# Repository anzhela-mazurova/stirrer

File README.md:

# stirrer
Magnetic stirrer for 1 US gallon bottle. The following information is provided:

1. Mechanical drawings of all 3D-printed parts in FreeCAD format.
2. Electronics Schematic and Board design in Eagle CAD format.
3. Source code of Board firmware.

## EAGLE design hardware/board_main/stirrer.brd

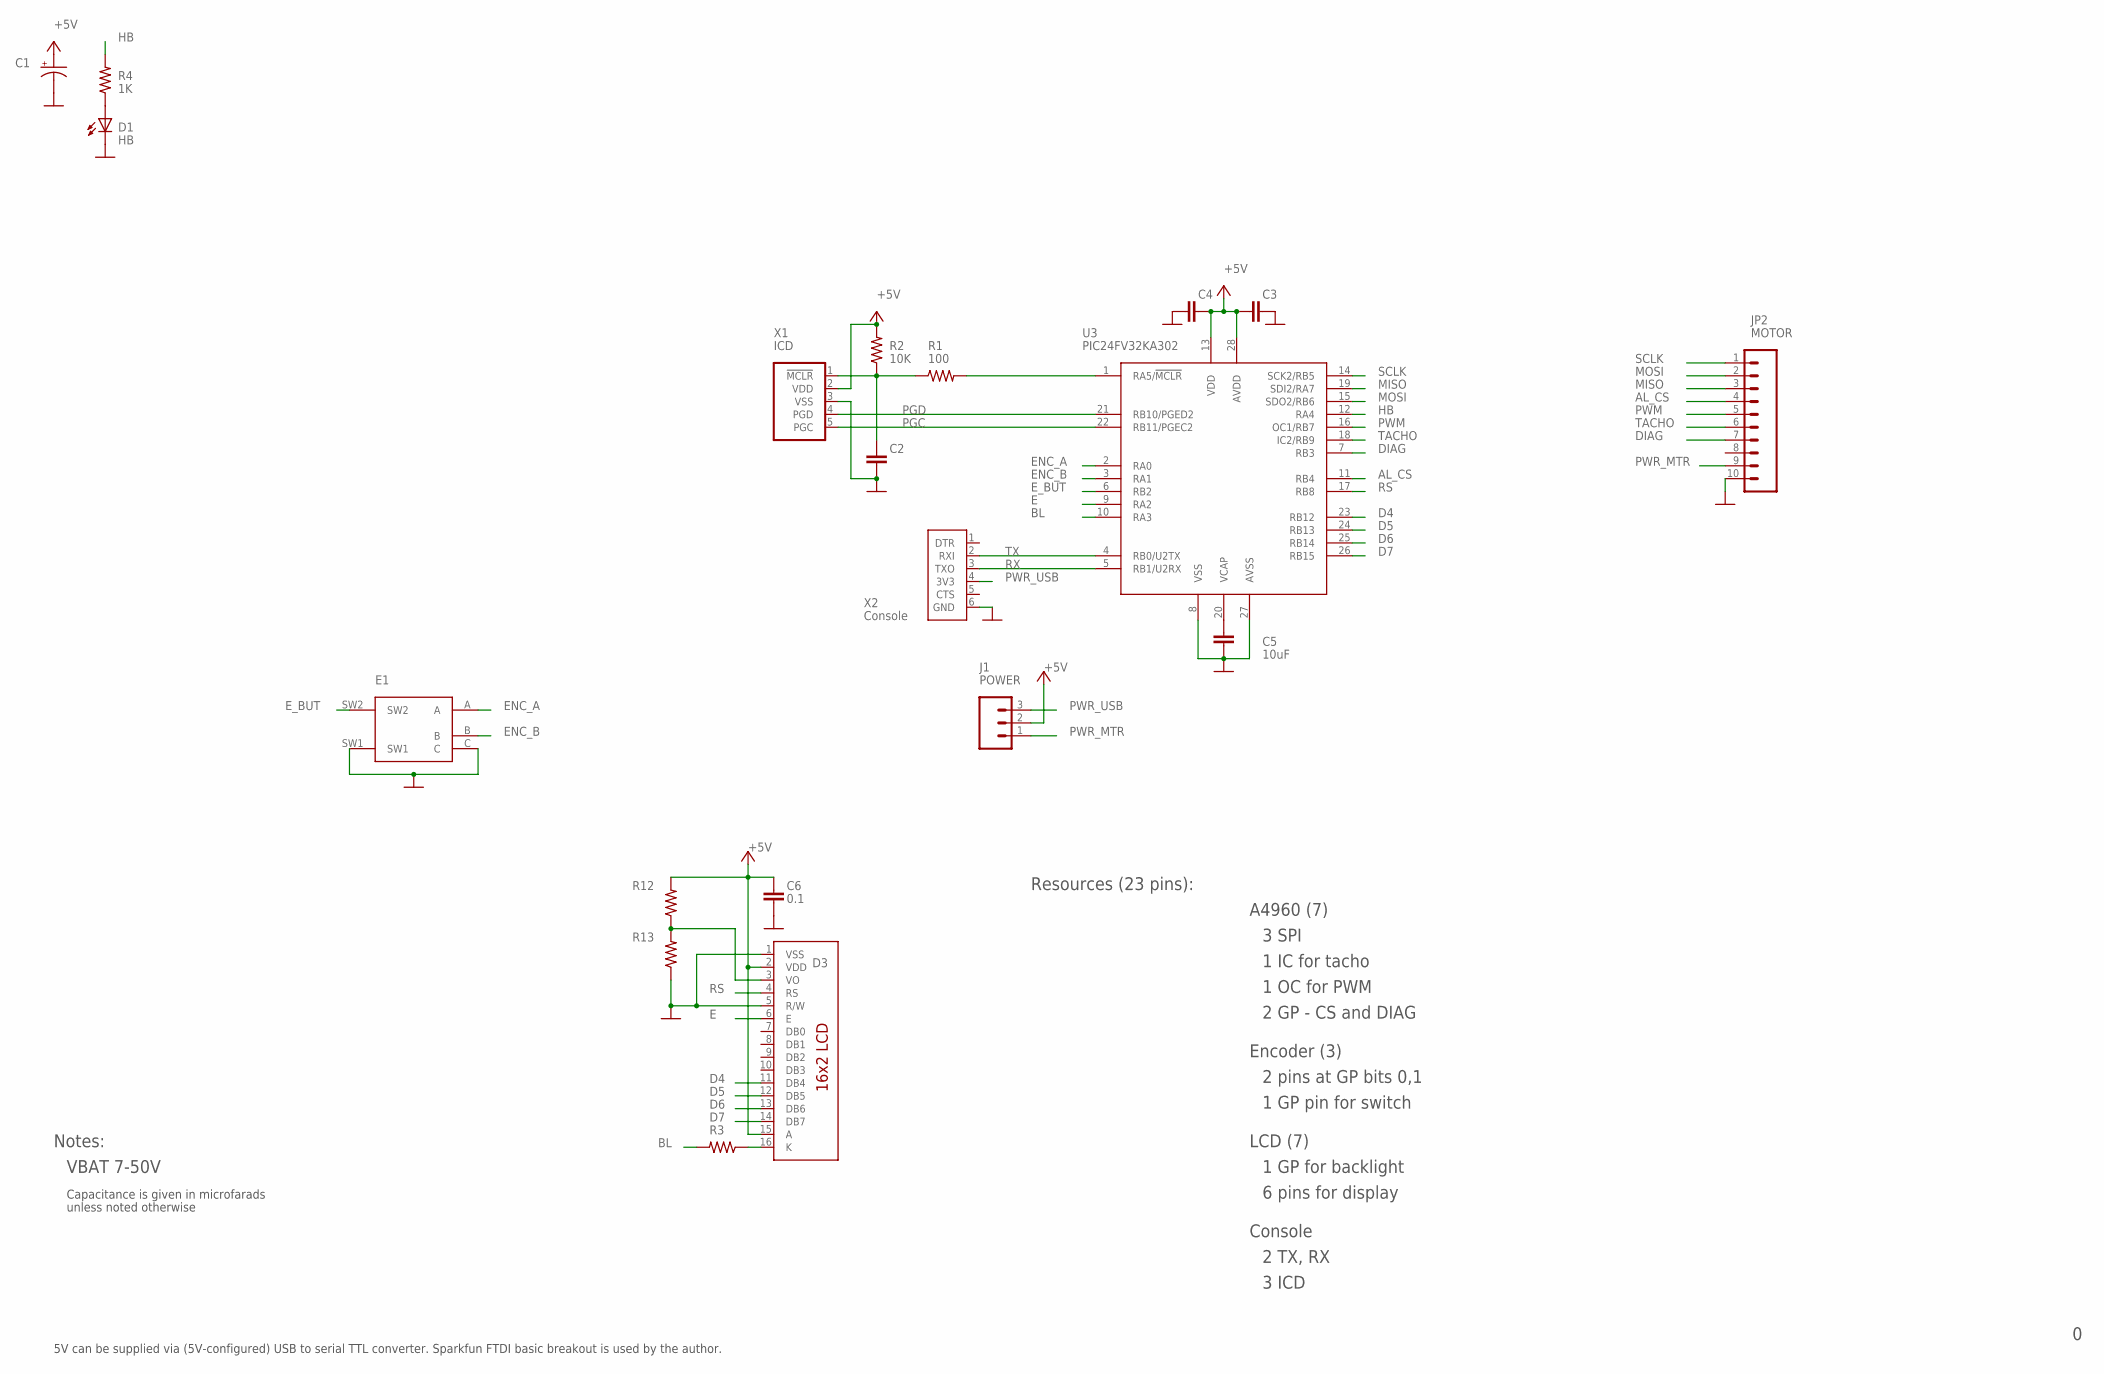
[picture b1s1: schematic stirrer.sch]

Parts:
C1: CAP_POL-RAD4; CAP_RAD_4MM
C2, C3, C4: 0.1uF; CAP-PTH-SMALL
C5: 10uF; CAP-PTH-SMALL
C6: 0.1; CAP-PTH-SMALL
D1: HB; LED5MM
D3: LCD-16X2-STD; LCD-16X2
E1: ROTARY_ENCODER_SWITCH-PEC12_HOR; ENC_12X14MM_SW_HOR
J1: POWER; 1X03
JP2: MOTOR; 1X10
R1: 100; AXIAL-0.4
R2: 10K; AXIAL-0.4
R3, R12, R13: RESISTOR-PTH04; AXIAL-0.4
R4: 1K; AXIAL-0.4
U3: PIC24FV32KA302; DIL28-3
X1: ICD; 1X05
X2: Console; 1X06

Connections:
+5V: C1.P (+), C3.1, C4.2, C6.2, D3.2 (VDD), D3.15 (A), J1.2, R2.P$2 (2), R12.P$2 (2), U3.13 (VDD), U3.28 (AVDD), X1.2 (VDD)
AL_CS: JP2.4, U3.11 (RB4)
BL: R3.P$2 (2), U3.10 (RA3)
D4: D3.11 (DB4), U3.23 (RB12)
D5: D3.12 (DB5), U3.24 (RB13)
D6: D3.13 (DB6), U3.25 (RB14)
D7: D3.14 (DB7), U3.26 (RB15)
DIAG: JP2.7, U3.7 (RB3)
E: D3.6 (E), U3.9 (RA2)
ENC_A: E1.A, U3.2 (RA0)
ENC_B: E1.B, U3.3 (RA1)
E_BUT: E1.SW2, U3.6 (RB2)
GND: C1.N (-), C2.1, C3.2, C4.1, C5.2, C6.1, D1.K (C), D3.1 (VSS), D3.5 (R/W), E1.C, E1.SW1, JP2.10, R13.P$1 (1), U3.8 (VSS), U3.27 (AVSS), X1.3 (VSS), X2.6 (GND)
HB: R4.P$2 (2), U3.12 (RA4)
MISO: JP2.3, U3.19 (SDI2/RA7)
MOSI: JP2.2, U3.15 (SDO2/RB6)
unnamed: C5.1, U3.20 (VCAP)
unnamed: R1.P$2 (2), U3.1 (RA5/!MCLR)
unnamed: D3.16 (K), R3.P$1 (1)
unnamed: D1.A, R4.P$1 (1)
unnamed: D3.3 (VO), R12.P$1 (1), R13.P$2 (2)
unnamed: C2.2, R1.P$1 (1), R2.P$1 (1), X1.1 (!MCLR)
PGC: U3.22 (RB11/PGEC2), X1.5 (PGC)
PGD: U3.21 (RB10/PGED2), X1.4 (PGD)
PWM: JP2.5, U3.16 (OC1/RB7)
PWR_MTR: J1.1, JP2.9
PWR_USB: J1.3, X2.4 (3V3)
RS: D3.4 (RS), U3.17 (RB8)
RX: U3.5 (RB1/U2RX), X2.3 (TXO)
SCLK: JP2.1, U3.14 (SCK2/RB5)
TACHO: JP2.6, U3.18 (IC2/RB9)
TX: U3.4 (RB0/U2TX), X2.2 (RXI)

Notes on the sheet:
Notes:
VBAT 7-50V
Resources (23 pins):
3 SPI
6 pins for display
2 GP - CS and DIAG
A4960 (7)
1 IC for tacho
1 OC for PWM
Encoder (3)
2 pins at GP bits 0,1
1 GP pin for switch
LCD (7)
1 GP for backlight
Console
2 TX, RX
3 ICD
Capacitance is given in microfarads
unless noted otherwise
5V can be supplied via (5V-configured) USB to serial TTL converter. Sparkfun FTDI basic breakout is used by the author.

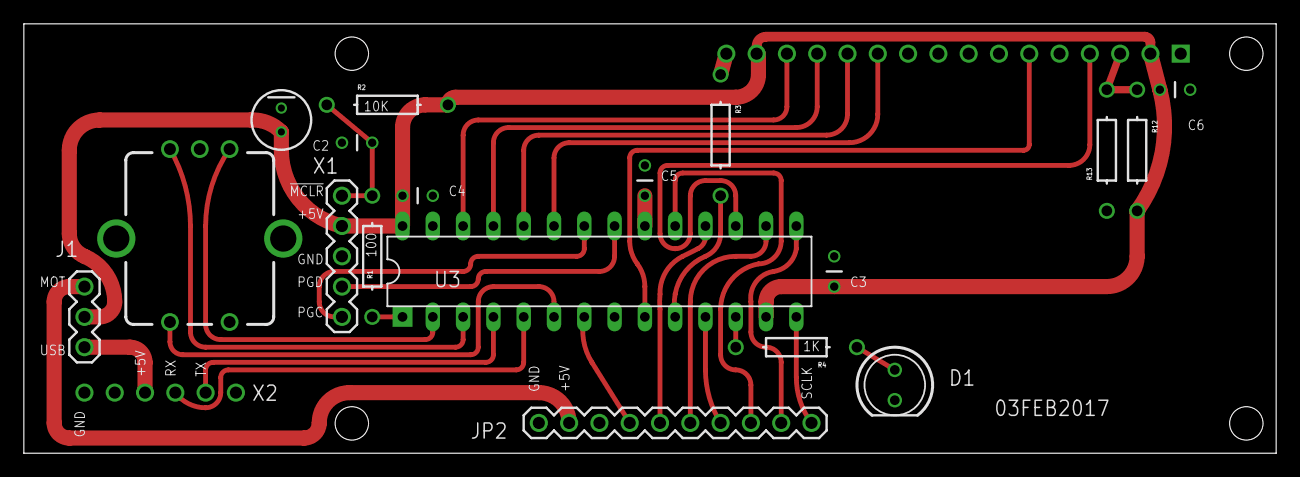
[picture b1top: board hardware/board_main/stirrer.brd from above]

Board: 2 copper layers, 105.0 x 36.0 mm, 20 parts (1 on the bottom side), 32 nets.

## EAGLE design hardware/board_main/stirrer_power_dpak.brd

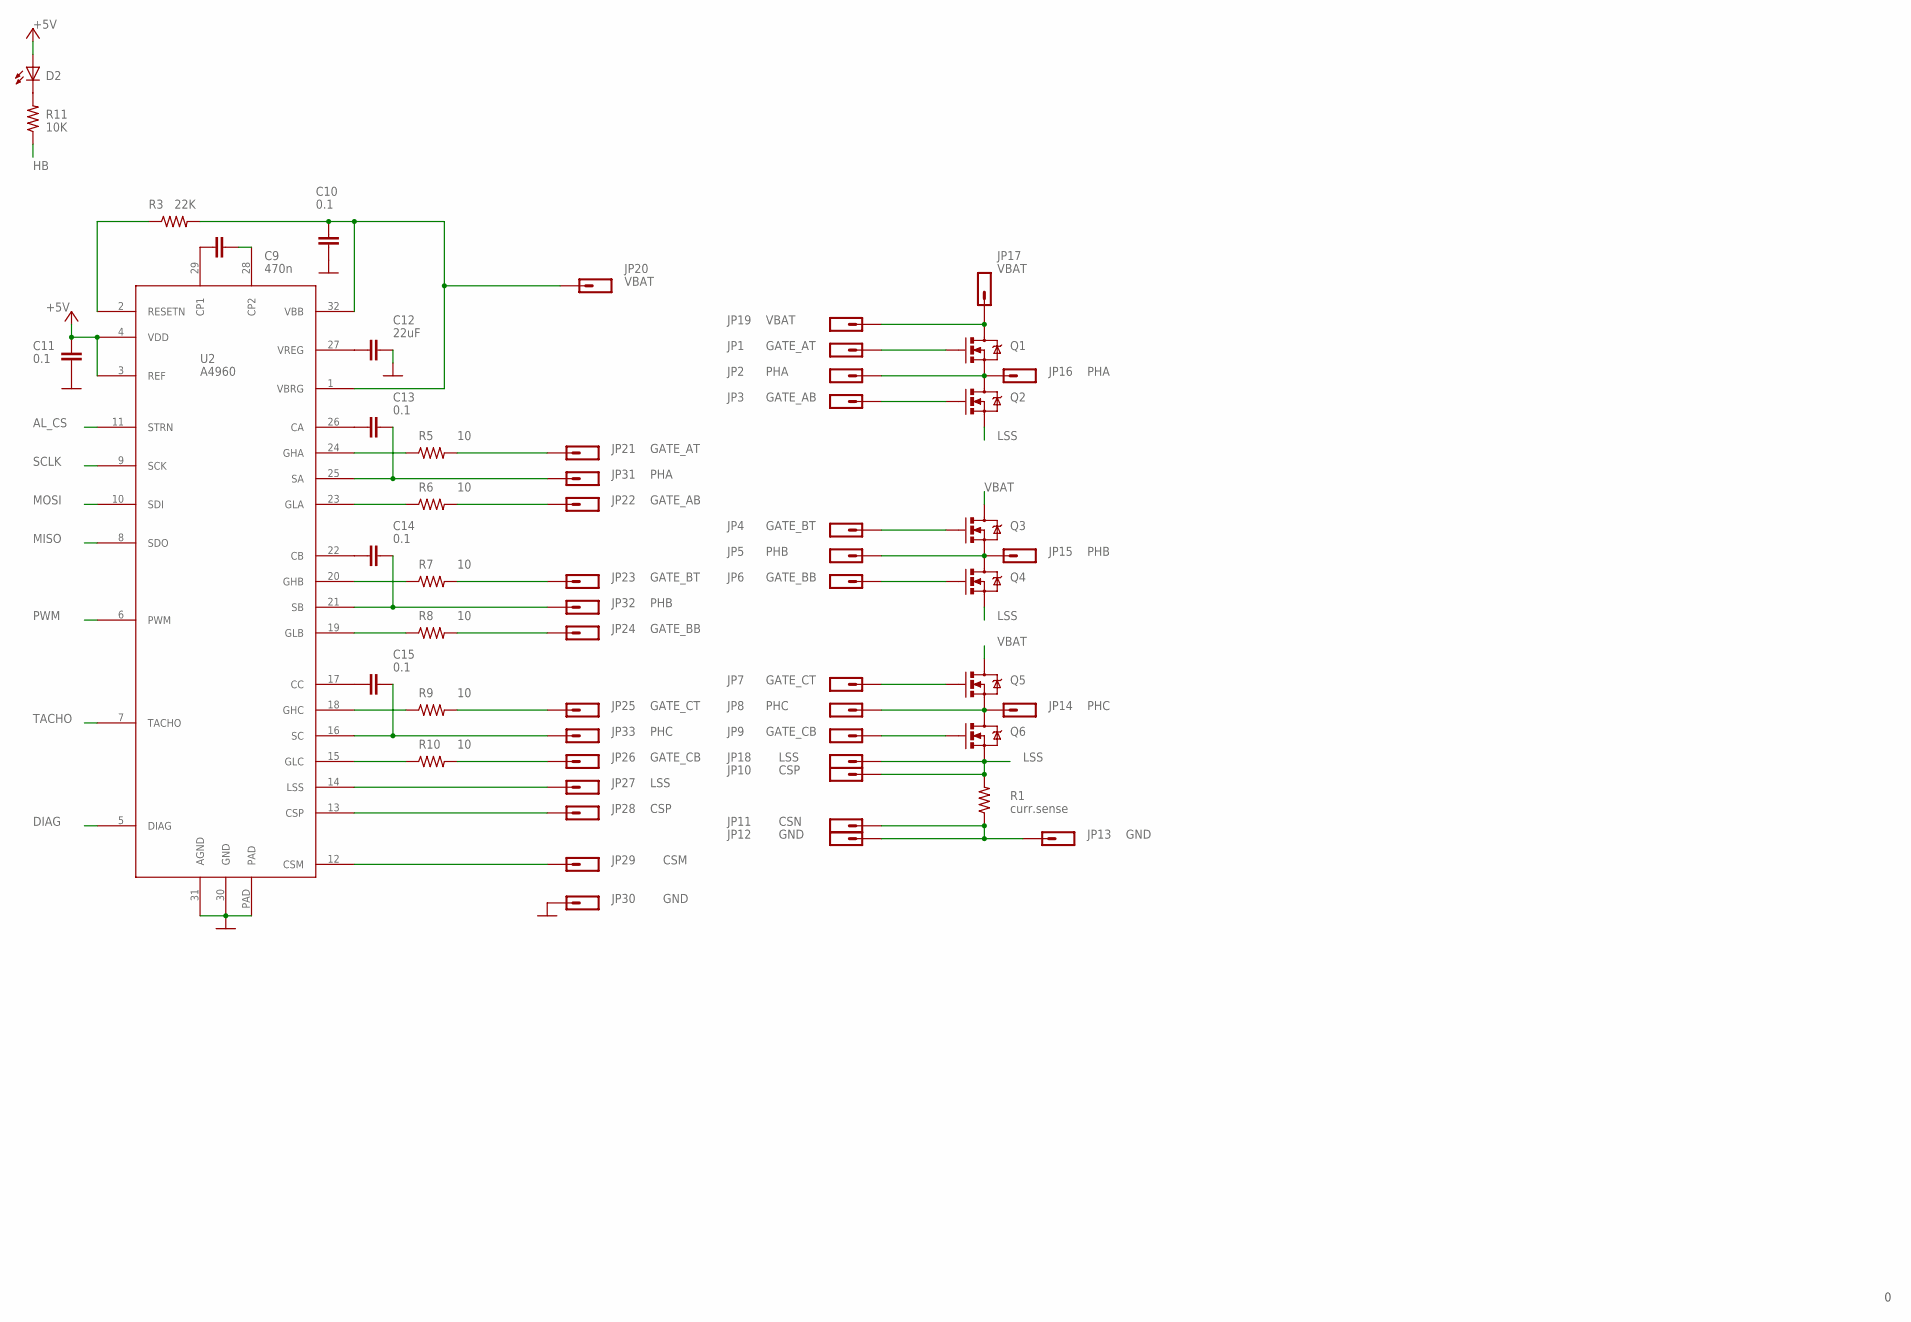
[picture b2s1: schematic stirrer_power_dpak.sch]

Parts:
C9: 470n; 0603
C10, C11, C13, C14, C15: 0.1; 0603
C12: 22uF; 1206
D2: LED5MM
JP1, JP21: GATE_AT; 1X01_TT
JP2, JP16, JP31: PHA; 1X01_TT
JP3, JP22: GATE_AB; 1X01_TT
JP4, JP23: GATE_BT; 1X01_TT
JP5, JP15, JP32: PHB; 1X01_TT
JP6, JP24: GATE_BB; 1X01_TT
JP7, JP25: GATE_CT; 1X01_TT
JP8, JP14, JP33: PHC; 1X01_TT
JP9, JP26: GATE_CB; 1X01_TT
JP10, JP28: CSP; 1X01_TT
JP11: CSN; 1X01_TT
JP12, JP13, JP30: GND; 1X01_TT
JP17, JP19, JP20: VBAT; 1X01_TT
JP18, JP27: LSS; 1X01_TT
JP29: CSM; 1X01_TT
Q1, Q2, Q3, Q4, Q5, Q6: MOSFET-NCHANNEL-DPAK; DPAK
R1: curr.sense; 2512
R3: 22K; 0603
R5, R6, R7, R8, R9, R10: 10; 0603
R11: 10K; 0603
U2: A4960; LQPF-32

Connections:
+5V: C11.2, D2.A, U2.3 (REF), U2.4 (VDD)
AL_CS: U2.11 (STRN)
CSM: JP29.1, U2.12 (CSM)
CSP: JP28.1, U2.13 (CSP)
DIAG: U2.5 (DIAG)
GATE_AB: JP22.1, R6.2
GATE_AT: JP21.1, R5.2
GATE_BB: JP24.1, R8.2
GATE_BT: JP23.1, R7.2
GATE_CB: JP26.1, R10.2
GATE_CT: JP25.1, R9.2
GND: C10.1, C11.1, C12.2, JP11.1, JP12.1, JP13.1, JP30.1, R1.P$1 (1), U2.30 (GND), U2.31 (AGND), U2.PAD
HB: R11.1
LSS: JP10.1, JP18.1, Q2.3 (S), Q4.3 (S), Q6.3 (S), R1.P$2 (2)
LSS1: JP27.1, U2.14 (LSS)
MISO: U2.8 (SDO)
MOSI: U2.10 (SDI)
unnamed: JP2.1, JP16.1, Q1.3 (S), Q2.4 (D)
unnamed: JP5.1, JP15.1, Q3.3 (S), Q4.4 (D)
unnamed: JP8.1, JP14.1, Q5.3 (S), Q6.4 (D)
unnamed: JP1.1, Q1.1 (G)
unnamed: JP3.1, Q2.1 (G)
unnamed: C9.1, U2.29 (CP1)
unnamed: C9.2, U2.28 (CP2)
unnamed: R3.1, U2.2 (RESETN)
unnamed: D2.K (C), R11.2
unnamed: JP4.1, Q3.1 (G)
unnamed: JP6.1, Q4.1 (G)
unnamed: JP7.1, Q5.1 (G)
unnamed: JP9.1, Q6.1 (G)
unnamed: C12.1, U2.27 (VREG)
unnamed: C13.2, U2.26 (CA)
unnamed: C14.2, U2.22 (CB)
unnamed: C15.2, U2.17 (CC)
unnamed: C13.1, JP31.1, U2.25 (SA)
unnamed: C14.1, JP32.1, U2.21 (SB)
unnamed: C15.1, JP33.1, U2.16 (SC)
unnamed: R5.1, U2.24 (GHA)
unnamed: R7.1, U2.20 (GHB)
unnamed: R9.1, U2.18 (GHC)
unnamed: R6.1, U2.23 (GLA)
unnamed: R8.1, U2.19 (GLB)
unnamed: R10.1, U2.15 (GLC)
PWM: U2.6 (PWM)
SCLK: U2.9 (SCK)
TACHO: U2.7 (TACHO)
VBAT: JP17.1, JP19.1, Q1.4 (D), Q3.4 (D), Q5.4 (D)
VBAT1: C10.2, JP20.1, R3.2, U2.1 (VBRG), U2.32 (VBB)

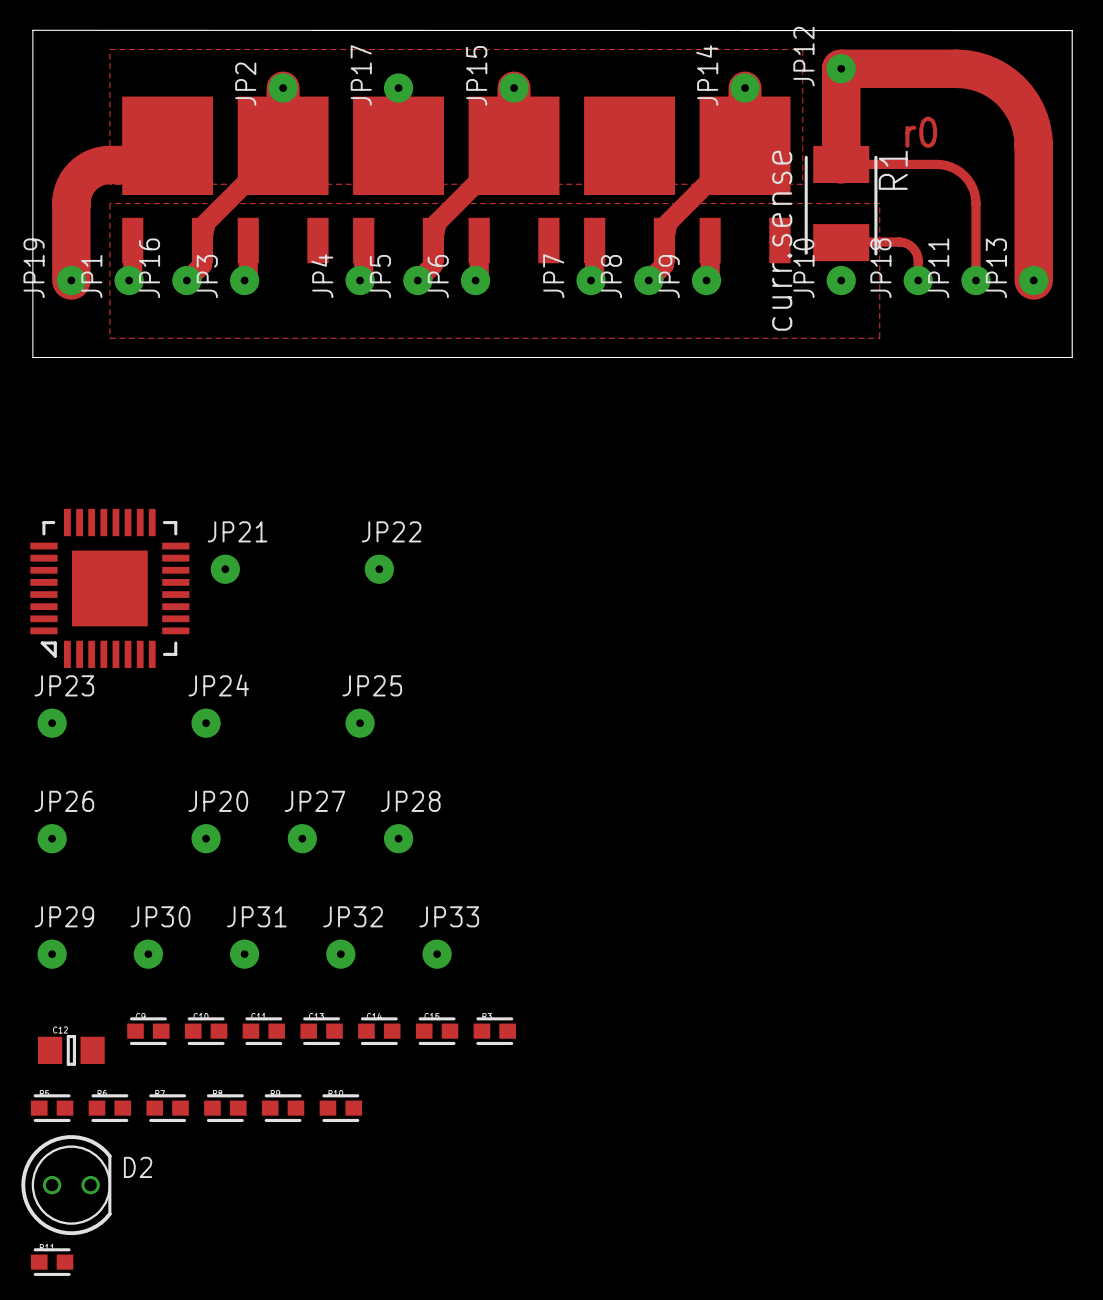
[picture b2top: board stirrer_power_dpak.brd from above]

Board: 2 copper layers, 68.6 x 21.6 mm, 57 parts (0 on the bottom side), 40 nets.

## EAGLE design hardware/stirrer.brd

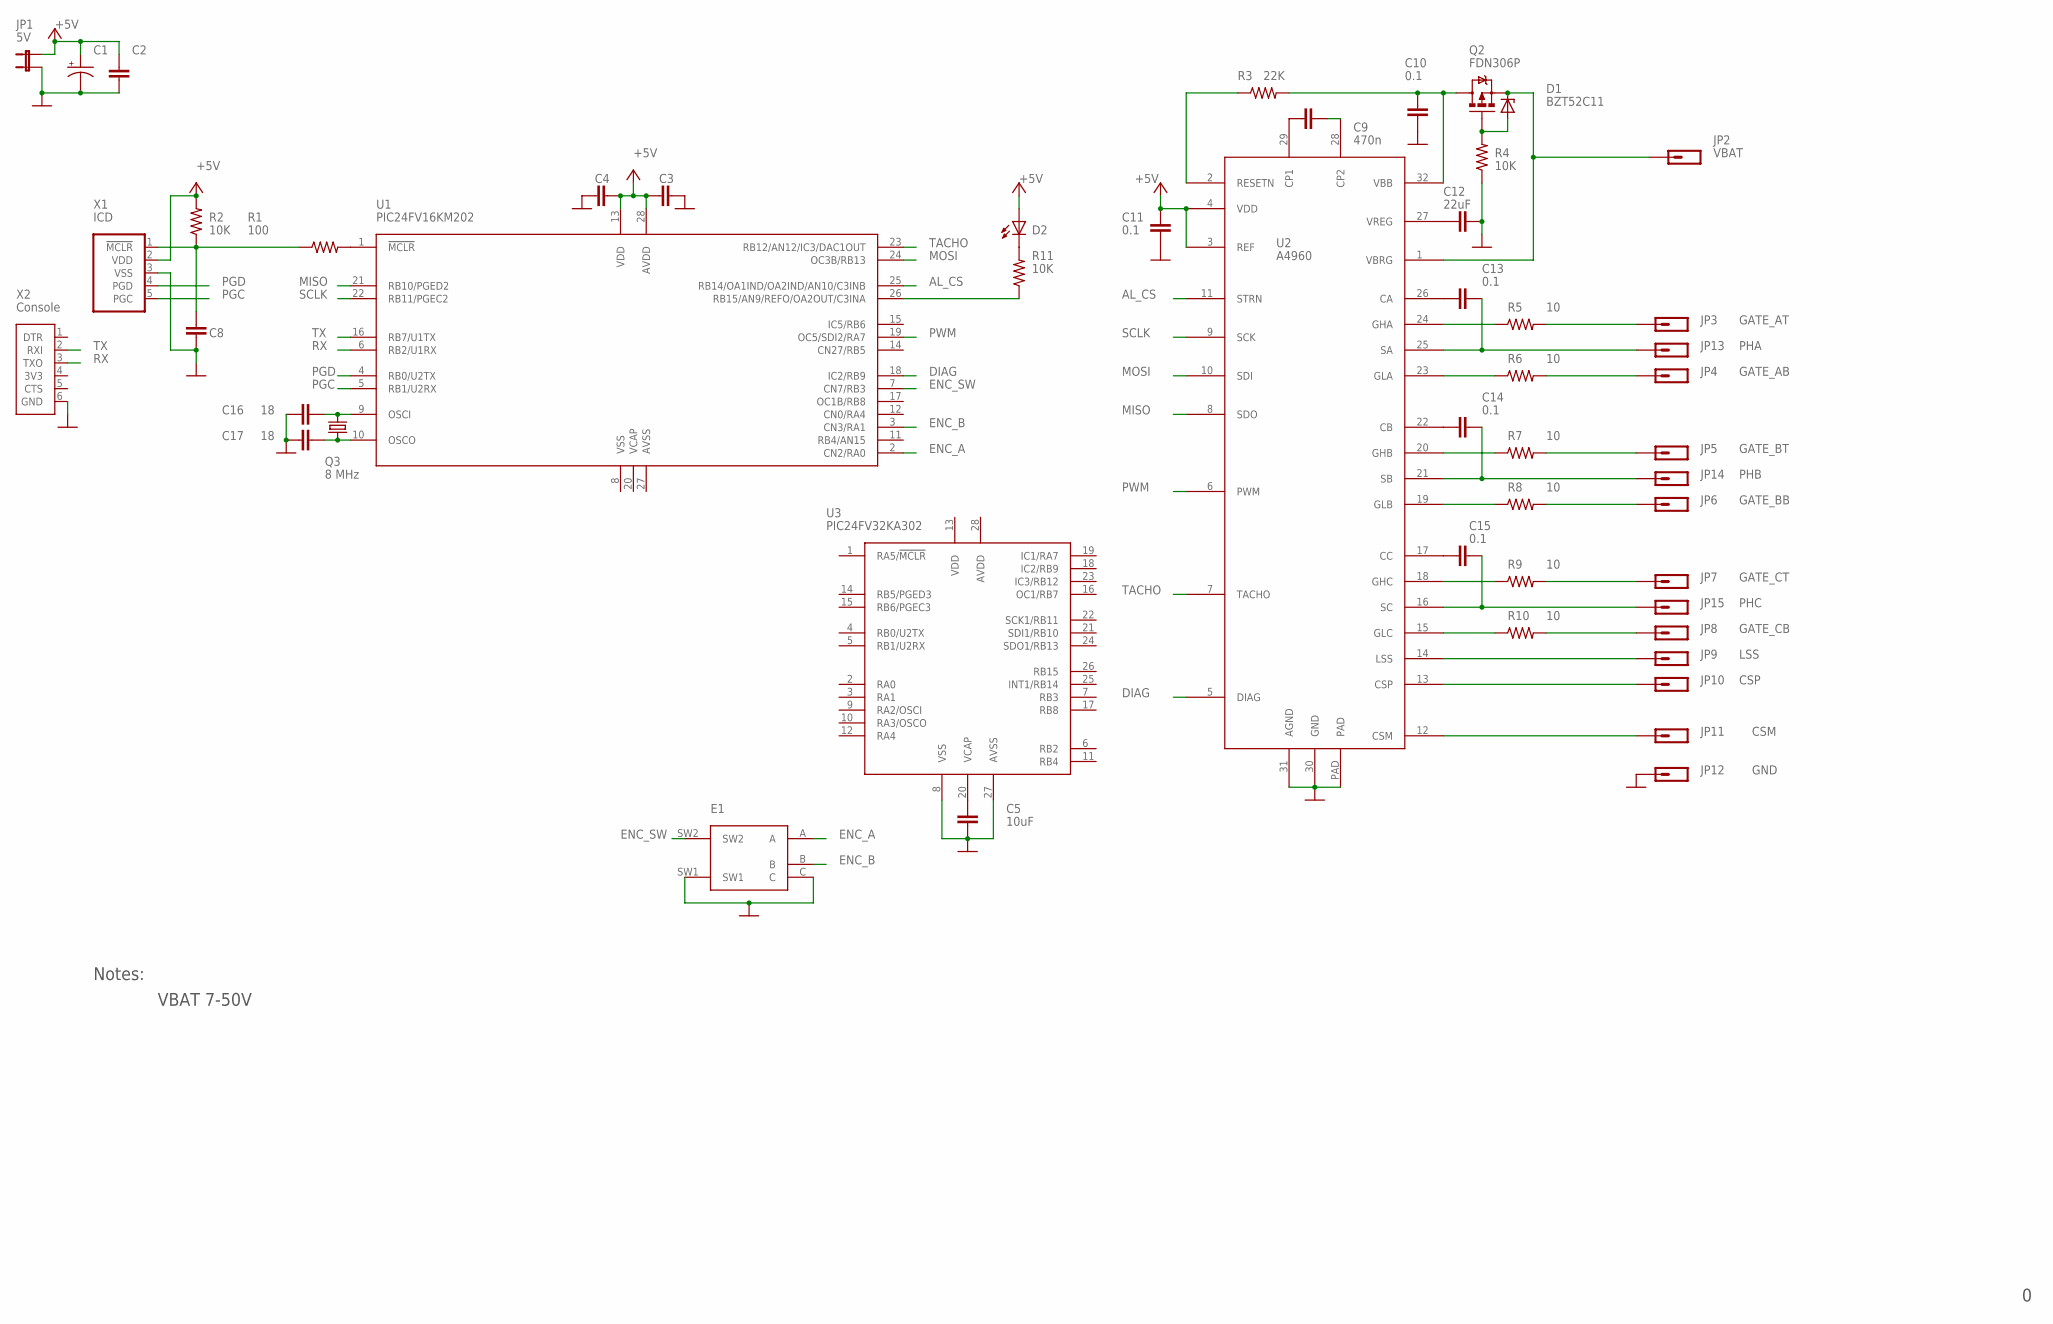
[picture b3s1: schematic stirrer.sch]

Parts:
C1: CAP_POL-RAD8; CAP_RAD_8MM
C2: CAP0603; 0603
C3, C4, C8: 0.1uF; 0603
C5: 10uF; 0603
C9: 470n; 0603
C10, C11, C13, C14, C15: 0.1; 0603
C12: 22uF; 1206
C16, C17: 18; 0603
D1: BZT52C11; SOD-123
D2: LED5MM
E1: ROTARY_ENCODER_SWITCH-LUT; PEC12-LUT
JP1: 5V; 1X02
JP2: VBAT; 1X01_TT
JP3: GATE_AT; 1X01_TT
JP4: GATE_AB; 1X01_TT
JP5: GATE_BT; 1X01_TT
JP6: GATE_BB; 1X01_TT
JP7: GATE_CT; 1X01_TT
JP8: GATE_CB; 1X01_TT
JP9: LSS; 1X01_TT
JP10: CSP; 1X01_TT
JP11: CSM; 1X01_TT
JP12: GND; 1X01_TT
JP13: PHA; 1X01_TT
JP14: PHB; 1X01_TT
JP15: PHC; 1X01_TT
Q2: FDN306P; DPAK
Q3: 8 MHz; HC49US
R1: 100; 0603
R2, R4, R11: 10K; 0603
R3: 22K; 0603
R5, R6, R7, R8, R9, R10: 10; 0603
U1: PIC24FV16KM202; DIL28-3
U2: A4960; LQPF-32
U3: PIC24FV32KA302; DIL28-3
X1: ICD; 1X05-TT
X2: Console; 1X06TT

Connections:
+5V: C1.P (+), C2.1, C3.1, C4.2, C11.2, D2.A, JP1.2, R2.2, U1.13 (VDD), U1.28 (AVDD), U2.3 (REF), U2.4 (VDD), X1.2 (VDD)
AL_CS: U1.25 (RB14/OA1IND/OA2IND/AN10/C3INB), U2.11 (STRN)
CSM: JP11.1, U2.12 (CSM)
CSP: JP10.1, U2.13 (CSP)
DIAG: U1.18 (IC2/RB9), U2.5 (DIAG)
ENC_A: E1.A, U1.2 (CN2/RA0)
ENC_B: E1.B, U1.3 (CN3/RA1)
ENC_SW: E1.SW2, U1.7 (CN7/RB3)
GATE_AB: JP4.1, R6.2
GATE_AT: JP3.1, R5.2
GATE_BB: JP6.1, R8.2
GATE_BT: JP5.1, R7.2
GATE_CB: JP8.1, R10.2
GATE_CT: JP7.1, R9.2
GND: C1.N (-), C2.2, C3.2, C4.1, C5.2, C8.1, C10.1, C11.1, C12.2, C16.1, C17.1, E1.C, E1.SW1, JP1.1, JP12.1, R4.1, U2.30 (GND), U2.31 (AGND), U2.PAD, U3.8 (VSS), U3.27 (AVSS), X1.3 (VSS), X2.6 (GND)
LSS: JP9.1, U2.14 (LSS)
MISO: U1.21 (RB10/PGED2), U2.8 (SDO)
MOSI: U1.24 (OC3B/RB13), U2.10 (SDI)
unnamed: C5.1, U3.20 (VCAP)
unnamed: R1.2, U1.1 (!MCLR)
unnamed: R11.1, U1.26 (RB15/AN9/REFO/OA2OUT/C3INA)
unnamed: C9.1, U2.29 (CP1)
unnamed: D2.K (C), R11.2
unnamed: C9.2, U2.28 (CP2)
unnamed: C8.2, R1.1, R2.1, X1.1 (!MCLR)
unnamed: R3.1, U2.2 (RESETN)
unnamed: C10.2, Q2.4 (D), R3.2, U2.32 (VBB)
unnamed: C12.1, U2.27 (VREG)
unnamed: C13.2, U2.26 (CA)
unnamed: D1.A, Q2.1 (G), R4.2
unnamed: C14.2, U2.22 (CB)
unnamed: C15.2, U2.17 (CC)
unnamed: C13.1, JP13.1, U2.25 (SA)
unnamed: C14.1, JP14.1, U2.21 (SB)
unnamed: C15.1, JP15.1, U2.16 (SC)
unnamed: R5.1, U2.24 (GHA)
unnamed: R7.1, U2.20 (GHB)
unnamed: R9.1, U2.18 (GHC)
unnamed: R6.1, U2.23 (GLA)
unnamed: R8.1, U2.19 (GLB)
unnamed: R10.1, U2.15 (GLC)
unnamed: C16.2, Q3.2, U1.9 (OSCI)
unnamed: C17.2, Q3.1, U1.10 (OSCO)
PGC: U1.5 (RB1/U2RX), X1.5 (PGC)
PGD: U1.4 (RB0/U2TX), X1.4 (PGD)
PWM: U1.19 (OC5/SDI2/RA7), U2.6 (PWM)
RX: U1.6 (RB2/U1RX), X2.3 (TXO)
SCLK: U1.22 (RB11/PGEC2), U2.9 (SCK)
TACHO: U1.23 (RB12/AN12/IC3/DAC1OUT), U2.7 (TACHO)
TX: U1.16 (RB7/U1TX), X2.2 (RXI)
VBAT: D1.K (C), JP2.1, Q2.3 (S), U2.1 (VBRG)

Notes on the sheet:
Notes:
VBAT 7-50V

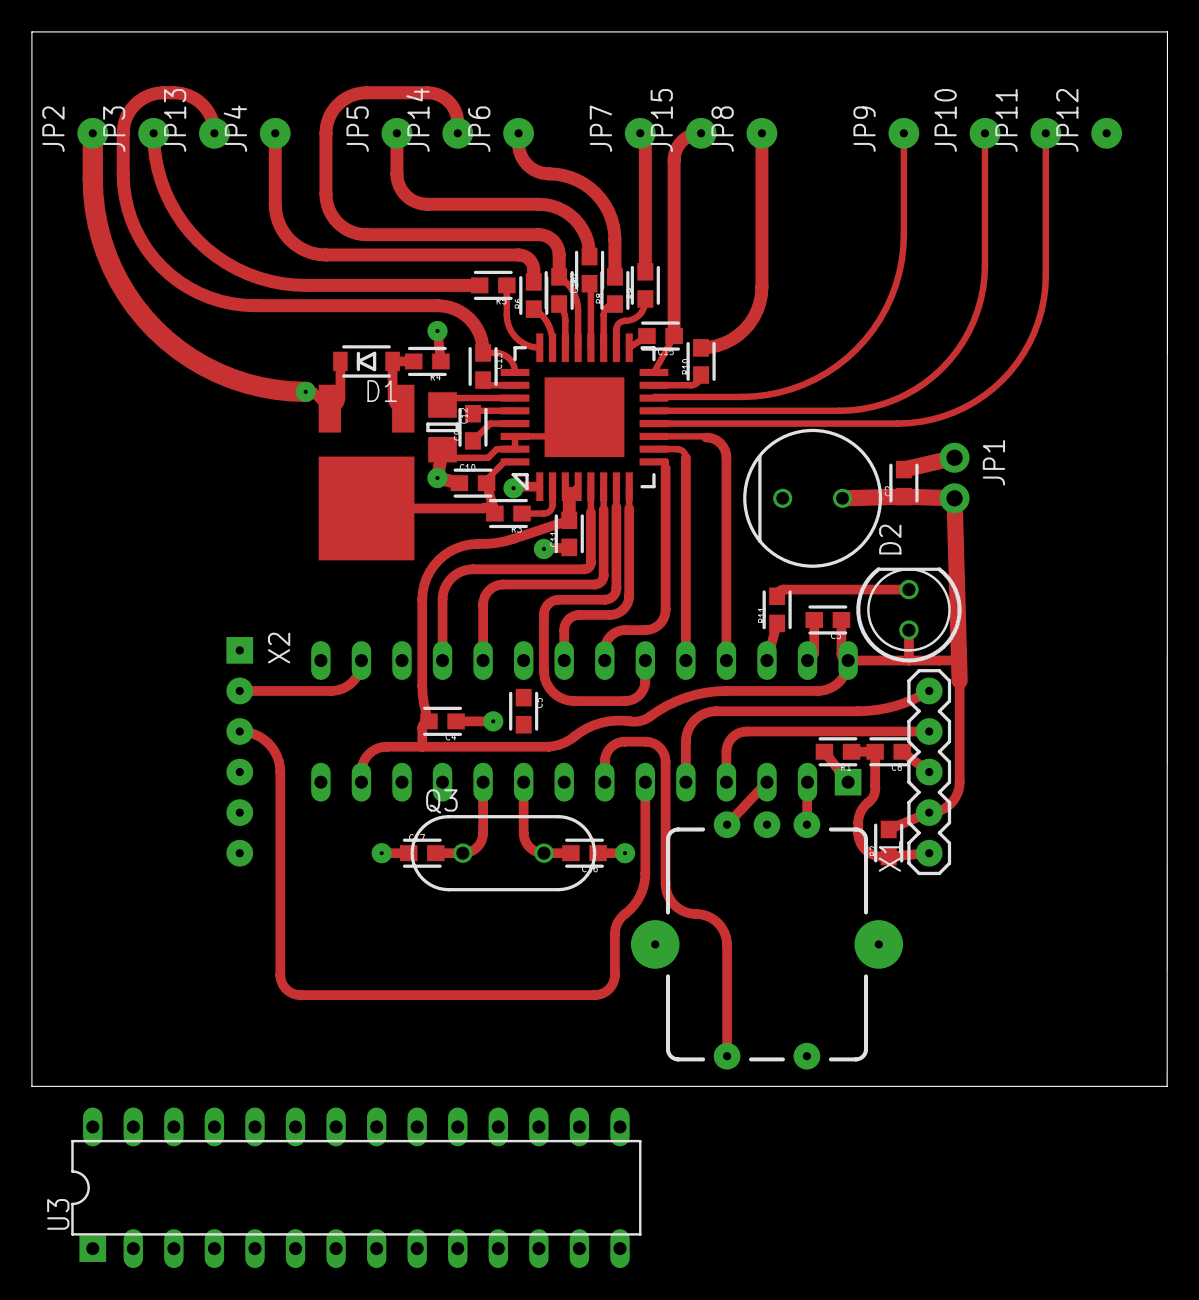
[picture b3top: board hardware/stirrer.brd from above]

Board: 2 copper layers, 71.1 x 66.0 mm, 51 parts (1 on the bottom side), 51 nets.

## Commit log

2017-01-07 initial commit to mechanical, hardware
2017-01-15 initial layout of display compartment
2017-01-15 added display compartment file
2017-01-16 display fits
2017-05-13 code section added
2017-05-13 fix take 2
2017-05-13 fix 3
2017-05-13 p24 port added
